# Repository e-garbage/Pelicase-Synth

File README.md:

# Pelicase-Synth
This repo is a work in progress and regroups all necessary files to build my very specific modular live setup. 3d models, schematics, code and gerber are here :)

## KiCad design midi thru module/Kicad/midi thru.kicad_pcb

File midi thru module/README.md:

# Midi Thru utility module

This module splits Midi input signals into 4 useable streams:
    - 1 to a korg volca
    - 1 to the rockPi (or a korg volca depending of the configuration)
    - 1 to the modular eurorack section
    - 1 to a DIN plug as a midi thru ouput, to plug other gear in

It also include the IEC power connector for the whole system, the main power switch,
status LED for the +12v, -12v and +5v power rails and a Midi activity LED (as well as 2 DIN 5PIN connectors)

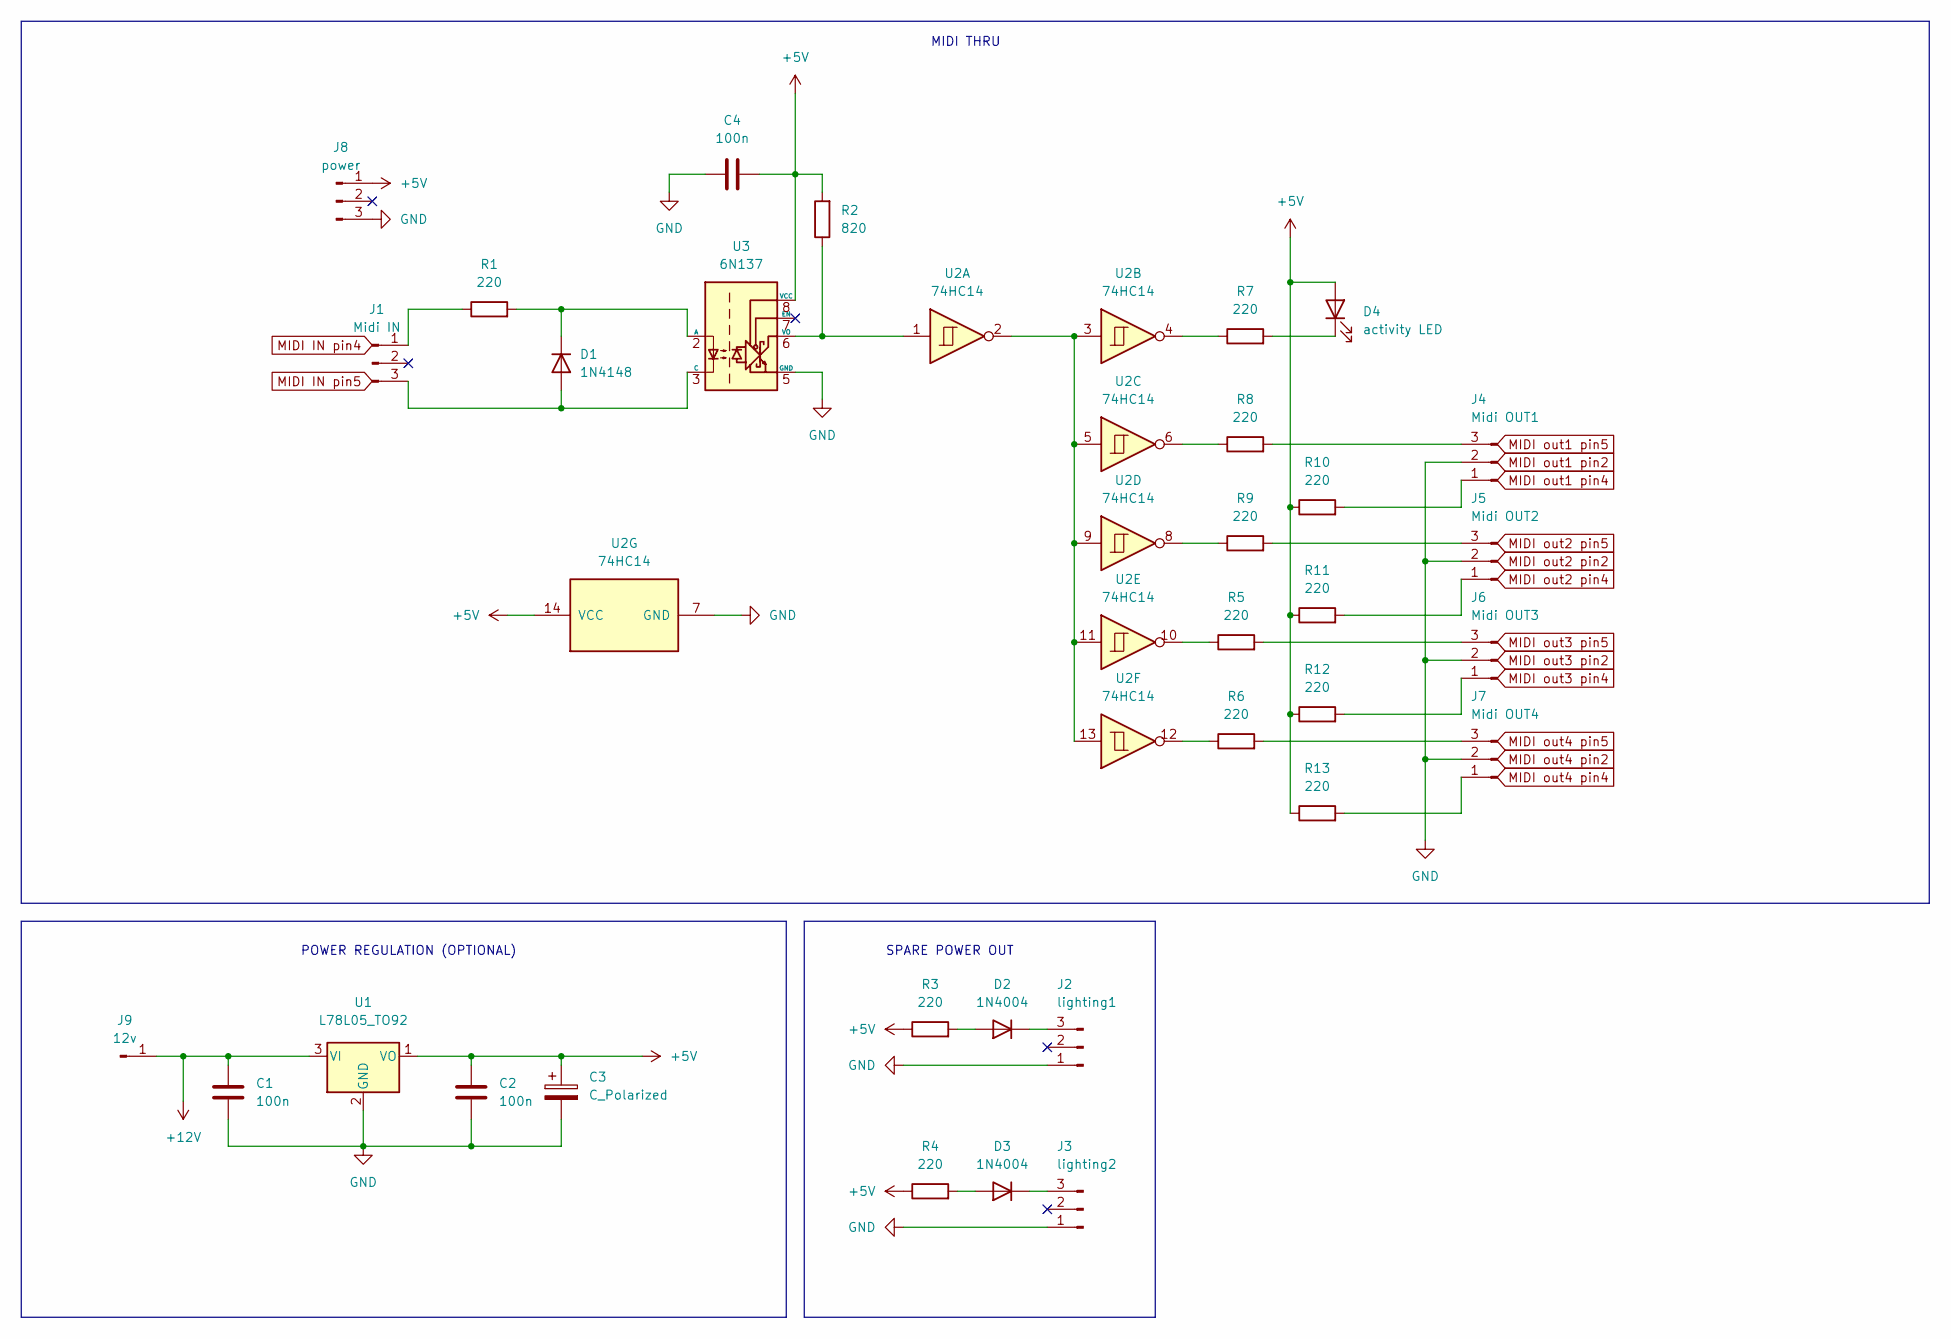
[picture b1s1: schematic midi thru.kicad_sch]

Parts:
C1, C2, C4: 100n; C_Disc_D3.8mm_W2.6mm_P2.50mm
C3: C_Polarized; CP_Radial_D4.0mm_P2.00mm
D1: 1N4148; D_DO-35_SOD27_P7.62mm_Horizontal
D2, D3: 1N4004; D_DO-41_SOD81_P10.16mm_Horizontal
D4: activity LED; LED_D5.0mm
J1: Midi IN; JST_XH_B3B-XH-AM_1x03_P2.50mm_Vertical
J2: lighting1; JST_XH_B3B-XH-AM_1x03_P2.50mm_Vertical
J3: lighting2; JST_XH_B3B-XH-AM_1x03_P2.50mm_Vertical
J4: Midi OUT1; JST_XH_B3B-XH-AM_1x03_P2.50mm_Vertical
J5: Midi OUT2; JST_XH_B3B-XH-AM_1x03_P2.50mm_Vertical
J6: Midi OUT3; JST_XH_B3B-XH-AM_1x03_P2.50mm_Vertical
J7: Midi OUT4; JST_XH_B3B-XH-AM_1x03_P2.50mm_Vertical
J8: power; JST_XH_B3B-XH-AM_1x03_P2.50mm_Vertical
J9: 12v; PinSocket_1x01_P2.54mm_Vertical
R1, R3, R4, R5, R6, R7, R8, R9, R10, R11, R12, R13: 220; R_Axial_DIN0204_L3.6mm_D1.6mm_P5.08mm_Horizontal
R2: 820; R_Axial_DIN0204_L3.6mm_D1.6mm_P5.08mm_Horizontal
U1: L78L05_TO92; TO-92_Inline
U2: 74HC14; DIP-14_W7.62mm_LongPads
U3: 6N137; DIP-8_W7.62mm

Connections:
+5V: C2.2, C3.1, C4.2, D4.2 (A), J8.1, R2.2, R3.1, R4.1, R10.1, R11.1, R12.1, R13.1, U1.1 (VO), U2.14 (VCC), U3.8 (VCC)
+12V: C1.2, J9.1, U1.3 (VI)
GND: C1.1, C2.1, C3.2, C4.1, J2.1, J3.1, J4.2, J5.2, J6.2, J7.2, J8.3, U1.2 (GND), U2.7 (GND), U3.5 (GND)
unnamed: D1.1 (K), R1.2, U3.2 (A)
unnamed: D1.2 (A), J1.3, U3.3 (C)
unnamed: D2.1 (K), J2.3
unnamed: D2.2 (A), R3.2
unnamed: D3.1 (K), J3.3
unnamed: D3.2 (A), R4.2
unnamed: D4.1 (K), R7.2
unnamed: J1.1, R1.1
unnamed: J4.1, R10.2
unnamed: J4.3, R8.2
unnamed: J5.1, R11.2
unnamed: J5.3, R9.2
unnamed: J6.1, R12.2
unnamed: J6.3, R5.2
unnamed: J7.1, R13.2
unnamed: J7.3, R6.2
unnamed: R2.1, U2.1, U3.6 (VO)
unnamed: R5.1, U2.10
unnamed: R6.1, U2.12
unnamed: R7.1, U2.4
unnamed: R8.1, U2.6
unnamed: R9.1, U2.8
unnamed: U2.2, U2.3, U2.5, U2.9, U2.11, U2.13

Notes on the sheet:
POWER REGULATION (OPTIONAL)
MIDI THRU
SPARE POWER OUT

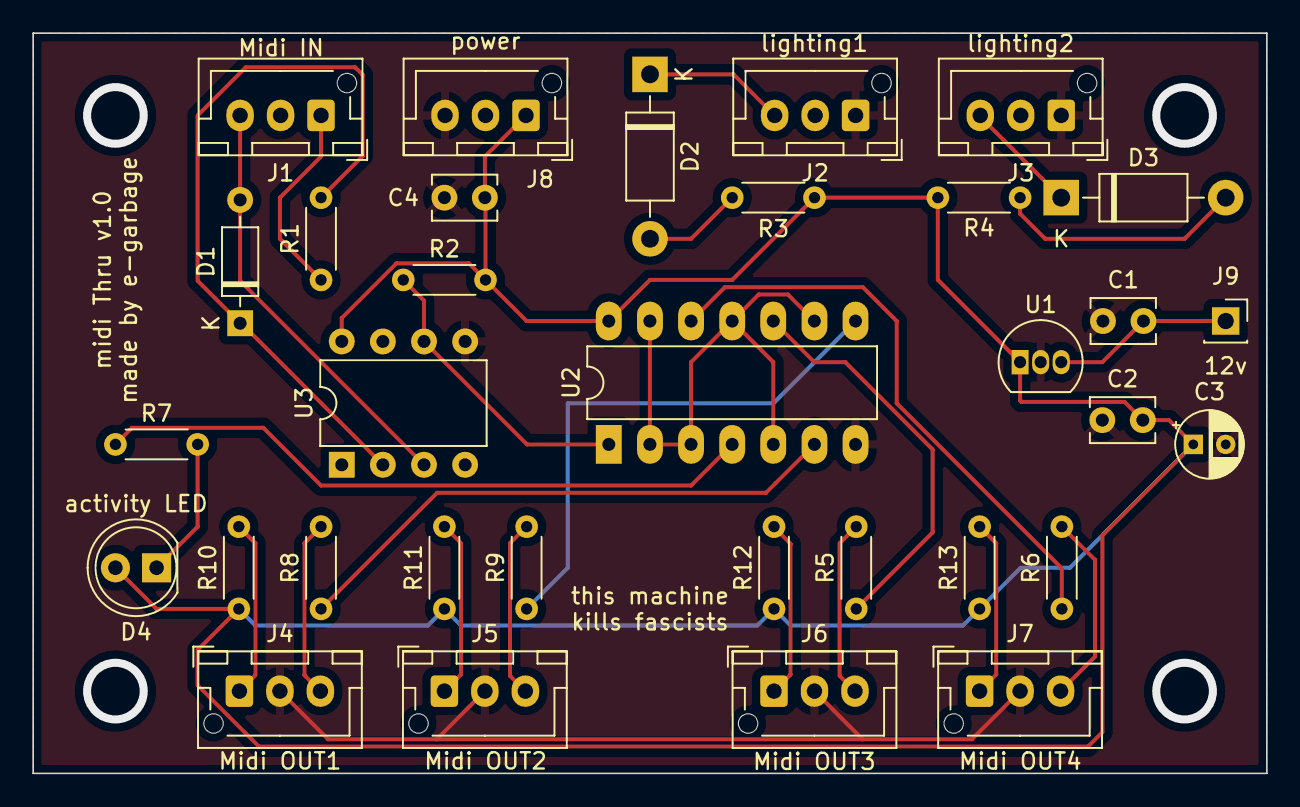
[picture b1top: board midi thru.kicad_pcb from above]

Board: 2 copper layers, 76.2 x 45.7 mm, 33 parts (0 on the bottom side), 26 nets.

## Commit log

2023-03-19 add license and readme
2023-03-19 image midi thru and folder structure
